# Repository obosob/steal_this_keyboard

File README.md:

# steal this keyboard!

here have a keyboard, it's not much -- supports kailh choc (PG1350) switches
with choc spacing, no diodes, promicro, reversable (2 pcbs makes 1 keyboard). 

## Disclaimer

THE SOFTWARE IS PROVIDED "AS IS", WITHOUT WARRANTY OF ANY KIND, EXPRESS OR
IMPLIED, INCLUDING BUT NOT LIMITED TO THE WARRANTIES OF MERCHANTABILITY,
FITNESS FOR A PARTICULAR PURPOSE AND NONINFRINGEMENT. IN NO EVENT SHALL THE
AUTHORS OR COPYRIGHT HOLDERS BE LIABLE FOR ANY CLAIM, DAMAGES OR OTHER
LIABILITY, WHETHER IN AN ACTION OF CONTRACT, TORT OR OTHERWISE, ARISING FROM,
OUT OF OR IN CONNECTION WITH THE SOFTWARE OR THE USE OR OTHER DEALINGS IN THE
SOFTWARE.

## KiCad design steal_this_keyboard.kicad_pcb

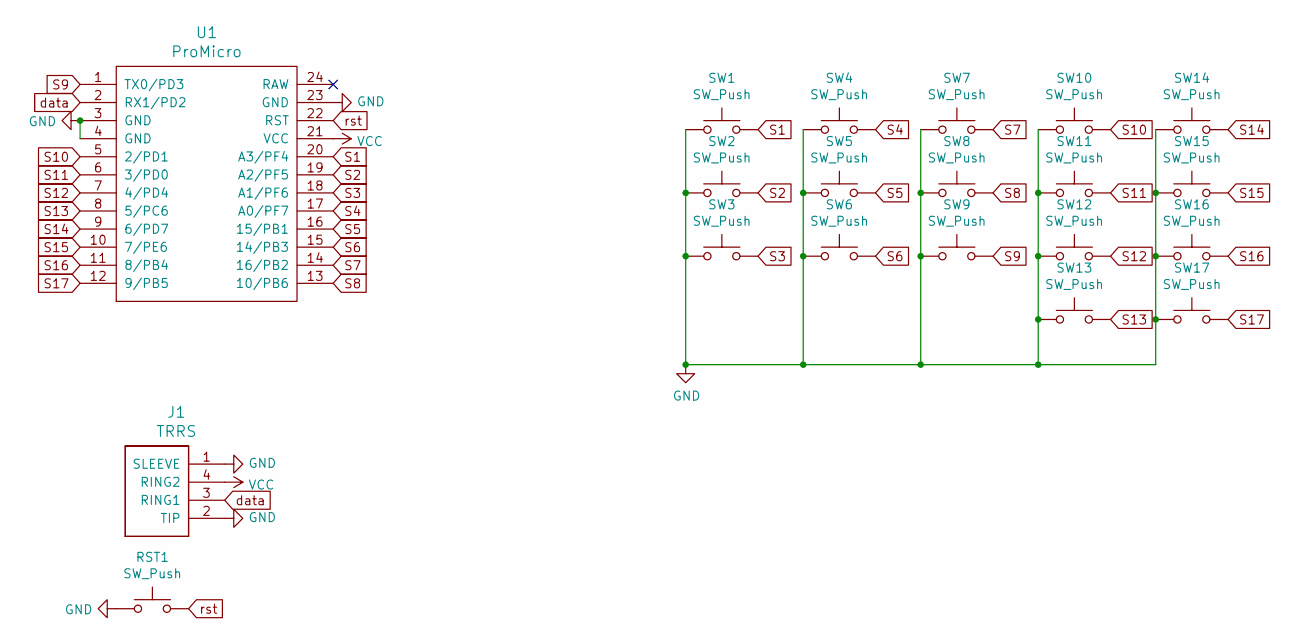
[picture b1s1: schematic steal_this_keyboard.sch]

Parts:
J1: TRRS; TRRS-PJ-320A-dual-squished
RST1: SW_Push; SW_Tactile_SPST_Angled_MJTP1117
SW1, SW2, SW3, SW4, SW5, SW6, SW7, SW8, SW9, SW10, SW11, SW12, SW13, SW14, SW15, SW16, SW17: SW_Push; Kailh-PG1350-1u-reversible
U1: ProMicro; ArduinoProMicro

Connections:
GND: J1.1 (SLEEVE), J1.2 (TIP), RST1.1, SW1.1, SW2.1, SW3.1, SW4.1, SW5.1, SW6.1, SW7.1, SW8.1, SW9.1, SW10.1, SW11.1, SW12.1, SW13.1, SW14.1, SW15.1, SW16.1, SW17.1, U1.3 (GND), U1.4 (GND), U1.23 (GND)
S1: SW1.2, U1.20 (A3/PF4)
S2: SW2.2, U1.19 (A2/PF5)
S3: SW3.2, U1.18 (A1/PF6)
S4: SW4.2, U1.17 (A0/PF7)
S5: SW5.2, U1.16 (15/PB1)
S6: SW6.2, U1.15 (14/PB3)
S7: SW7.2, U1.14 (16/PB2)
S8: SW8.2, U1.13 (10/PB6)
S9: SW9.2, U1.1 (TX0/PD3)
S10: SW10.2, U1.5 (2/PD1)
S11: SW11.2, U1.6 (3/PD0)
S12: SW12.2, U1.7 (4/PD4)
S13: SW13.2, U1.8 (5/PC6)
S14: SW14.2, U1.9 (6/PD7)
S15: SW15.2, U1.10 (7/PE6)
S16: SW16.2, U1.11 (8/PB4)
S17: SW17.2, U1.12 (9/PB5)
VCC: J1.4 (RING2), U1.21 (VCC)
data: J1.3 (RING1), U1.2 (RX1/PD2)
rst: RST1.2, U1.22 (RST)

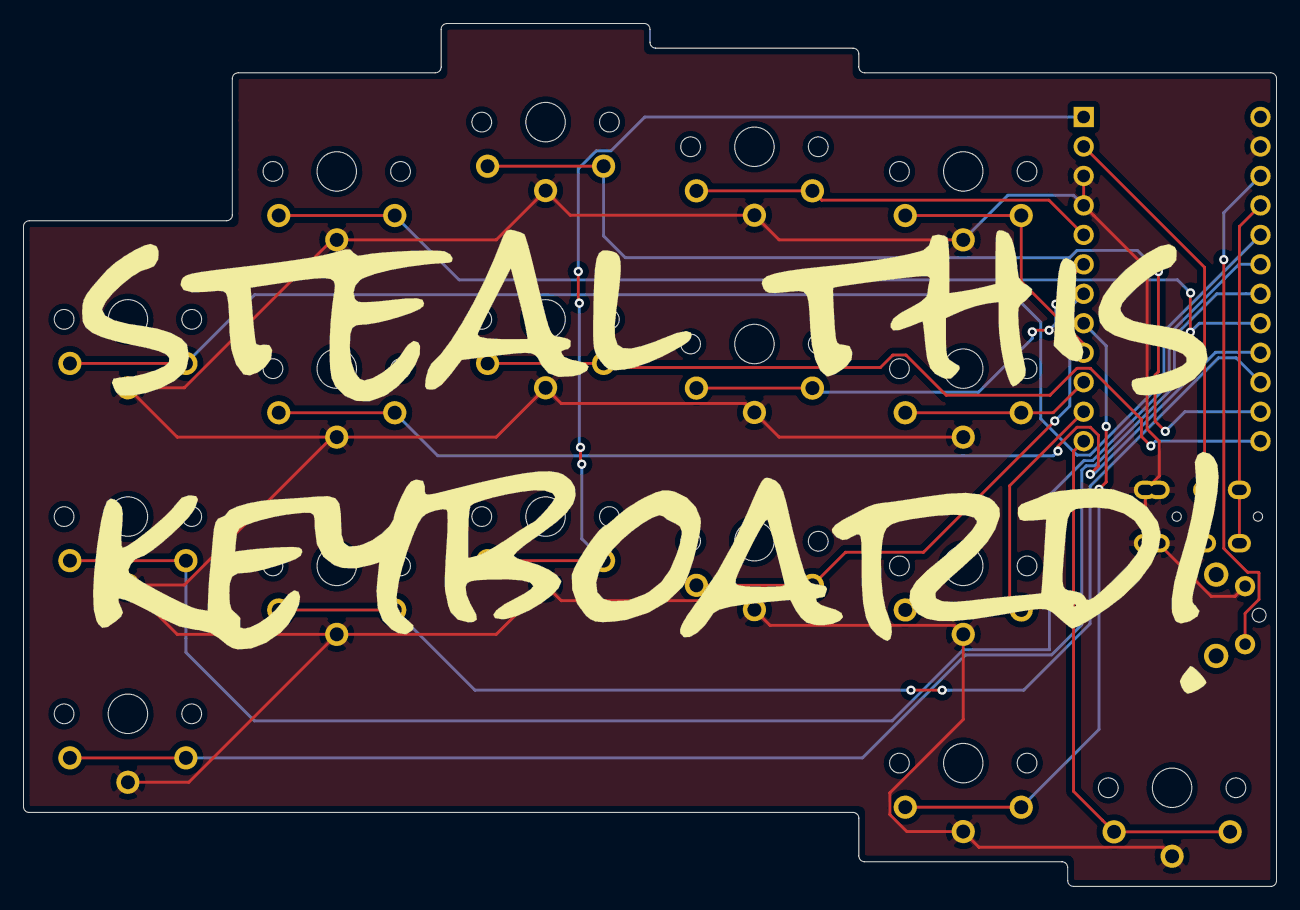
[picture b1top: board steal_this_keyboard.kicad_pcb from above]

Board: 2 copper layers, 108.0 x 74.4 mm, 20 parts (0 on the bottom side), 21 nets.

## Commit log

2021-05-13 Create project
2021-05-13 add libraries
2021-05-13 basic schematic
2021-05-13 place the things, route it badly, add silkscreen
2021-05-13 Add MIT License
2021-05-13 add readme
2021-05-14 de-weaponise the corners
